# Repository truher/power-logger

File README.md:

# Power Logger

Multichannel logger for residential power consumption measurement.
Reads two legs of 120v and a whole log of inductive current measurements.
Uses interrupts on the Teensy to avoid phase error.

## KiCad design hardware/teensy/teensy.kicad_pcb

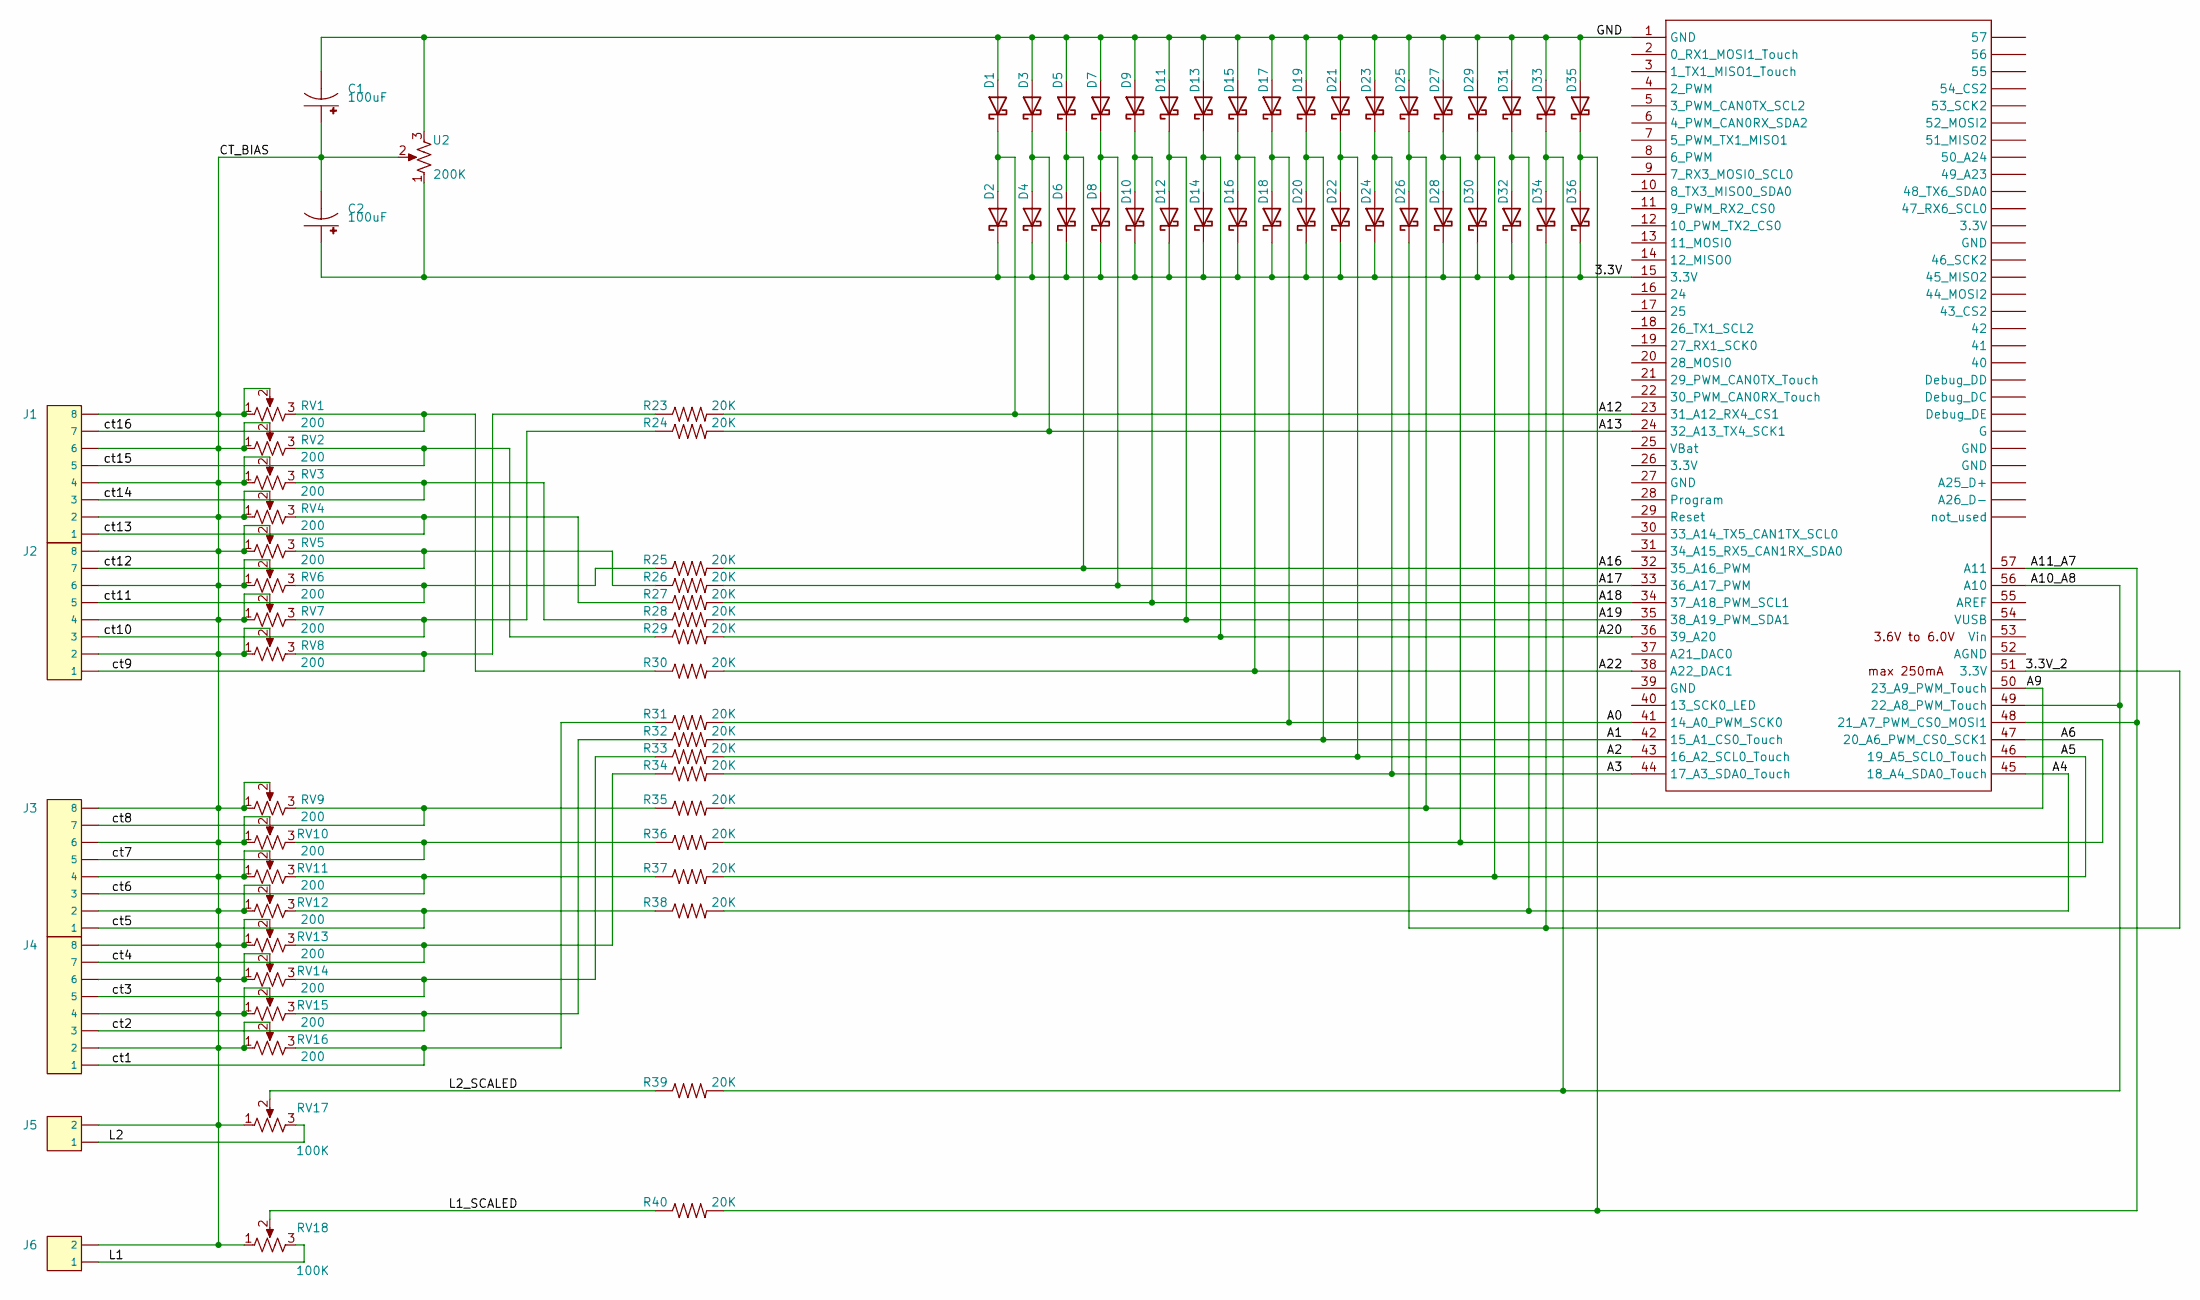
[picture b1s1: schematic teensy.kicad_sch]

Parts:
C1, C2: 100uF; CPOL-RADIAL-5MM-10MM
D1, D2, D3, D4, D5, D6, D7, D8, D9, D10, D11, D12, D13, D14, D15, D16, D17, D18, D19, D20, D21, D22, D23, D24, D25, D26, D27, D28, D29, D30, D31, D32, D33, D34, D35, D36: D_SOD-123
J1, J2, J3, J4: 1X08
J5, J6: 1X02
R23, R24, R25, R26, R27, R28, R29, R30, R31, R32, R33, R34, R35, R36, R37, R38, R39, R40: 20K; AXIAL-0.3
RV1, RV2, RV3, RV4, RV5, RV6, RV7, RV8, RV9, RV10, RV11, RV12, RV13, RV14, RV15, RV16: 200; Potentiometer_Bourns_3296W_Vertical
RV17, RV18: 100K; Potentiometer_Bourns_3296W_Vertical
U1: Teensy3.5; Teensy35_36_EMON
U2: 200K; Potentiometer_Bourns_3296W_Vertical

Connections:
/3.3V: C2.+, D2.1 (K), D4.1 (K), D6.1 (K), D8.1 (K), D10.1 (K), D12.1 (K), D14.1 (K), D16.1 (K), D18.1 (K), D20.1 (K), D22.1 (K), D24.1 (K), D28.1 (K), D30.1 (K), D32.1 (K), D36.1 (K), U1.15 (3.3V), U2.1
/3.3V_2: D26.1 (K), D34.1 (K), U1.51 (3.3V)
/A0: D17.1 (K), D18.2 (A), R31.P$2 (2), U1.41 (14_A0_PWM_SCK0)
/A1: D19.1 (K), D20.2 (A), R32.P$2 (2), U1.42 (15_A1_CS0_Touch)
/A2: D21.1 (K), D22.2 (A), R33.P$2 (2), U1.43 (16_A2_SCL0_Touch)
/A3: D23.1 (K), D24.2 (A), R34.P$2 (2), U1.44 (17_A3_SDA0_Touch)
/A4: D31.1 (K), D32.2 (A), R38.P$2 (2), U1.45 (18_A4_SDA0_Touch)
/A5: D29.1 (K), D30.2 (A), R37.P$2 (2), U1.46 (19_A5_SCL0_Touch)
/A6: D27.1 (K), D28.2 (A), R36.P$2 (2), U1.47 (20_A6_PWM_CS0_SCK1)
/A9: D25.1 (K), D26.2 (A), R35.P$2 (2), U1.50 (23_A9_PWM_Touch)
/A10_A8: D33.1 (K), D34.2 (A), R39.P$2 (2), U1.49 (22_A8_PWM_Touch), U1.56 (A10)
/A11_A7: D35.1 (K), D36.2 (A), R40.P$2 (2), U1.48 (21_A7_PWM_CS0_MOSI1), U1.57 (A11)
/A12: D1.1 (K), D2.2 (A), R23.P$2 (2), U1.23 (31_A12_RX4_CS1)
/A13: D3.1 (K), D4.2 (A), R24.P$2 (2), U1.24 (32_A13_TX4_SCK1)
/A16: D5.1 (K), D6.2 (A), R25.P$2 (2), U1.32 (35_A16_PWM)
/A17: D7.1 (K), D8.2 (A), R26.P$2 (2), U1.33 (36_A17_PWM)
/A18: D9.1 (K), D10.2 (A), R27.P$2 (2), U1.34 (37_A18_PWM_SCL1)
/A19: D11.1 (K), D12.2 (A), R28.P$2 (2), U1.35 (38_A19_PWM_SDA1)
/A20: D13.1 (K), D14.2 (A), R29.P$2 (2), U1.36 (39_A20)
/A22: D15.1 (K), D16.2 (A), R30.P$2 (2), U1.38 (A22_DAC1)
/CT_BIAS: C1.+, C2.-, J1.2, J1.4, J1.6, J1.8, J2.2, J2.4, J2.6, J2.8, J3.2, J3.4, J3.6, J3.8, J4.2, J4.4, J4.6, J4.8, J5.2, J6.2, RV1.1, RV1.2, RV2.1, RV2.2, RV3.1, RV3.2, RV4.1, RV4.2, RV5.1, RV5.2, RV6.1, RV6.2, RV7.1, RV7.2, RV8.1, RV8.2, RV9.1, RV9.2, RV10.1, RV10.2, RV11.1, RV11.2, RV12.1, RV12.2, RV13.1, RV13.2, RV14.1, RV14.2, RV15.1, RV15.2, RV16.1, RV16.2, RV17.1, RV18.1, U2.2
/GND: C1.-, D1.2 (A), D3.2 (A), D5.2 (A), D7.2 (A), D9.2 (A), D11.2 (A), D13.2 (A), D15.2 (A), D17.2 (A), D19.2 (A), D21.2 (A), D23.2 (A), D25.2 (A), D27.2 (A), D29.2 (A), D31.2 (A), D33.2 (A), D35.2 (A), U1.1 (GND), U2.3
/L1: J6.1, RV18.3
/L1_SCALED: R40.P$1 (1), RV18.2
/L2: J5.1, RV17.3
/L2_SCALED: R39.P$1 (1), RV17.2
/ct1: J4.1, R31.P$1 (1), RV16.3
/ct2: J4.3, R32.P$1 (1), RV15.3
/ct3: J4.5, R33.P$1 (1), RV14.3
/ct4: J4.7, R34.P$1 (1), RV13.3
/ct5: J3.1, R38.P$1 (1), RV12.3
/ct6: J3.3, R37.P$1 (1), RV11.3
/ct7: J3.5, R36.P$1 (1), RV10.3
/ct8: J3.7, R35.P$1 (1), RV9.3
/ct9: J2.1, R23.P$1 (1), RV8.3
/ct10: J2.3, R24.P$1 (1), RV7.3
/ct11: J2.5, R25.P$1 (1), RV6.3
/ct12: J2.7, R26.P$1 (1), RV5.3
/ct13: J1.1, R27.P$1 (1), RV4.3
/ct14: J1.3, R28.P$1 (1), RV3.3
/ct15: J1.5, R29.P$1 (1), RV2.3
/ct16: J1.7, R30.P$1 (1), RV1.3

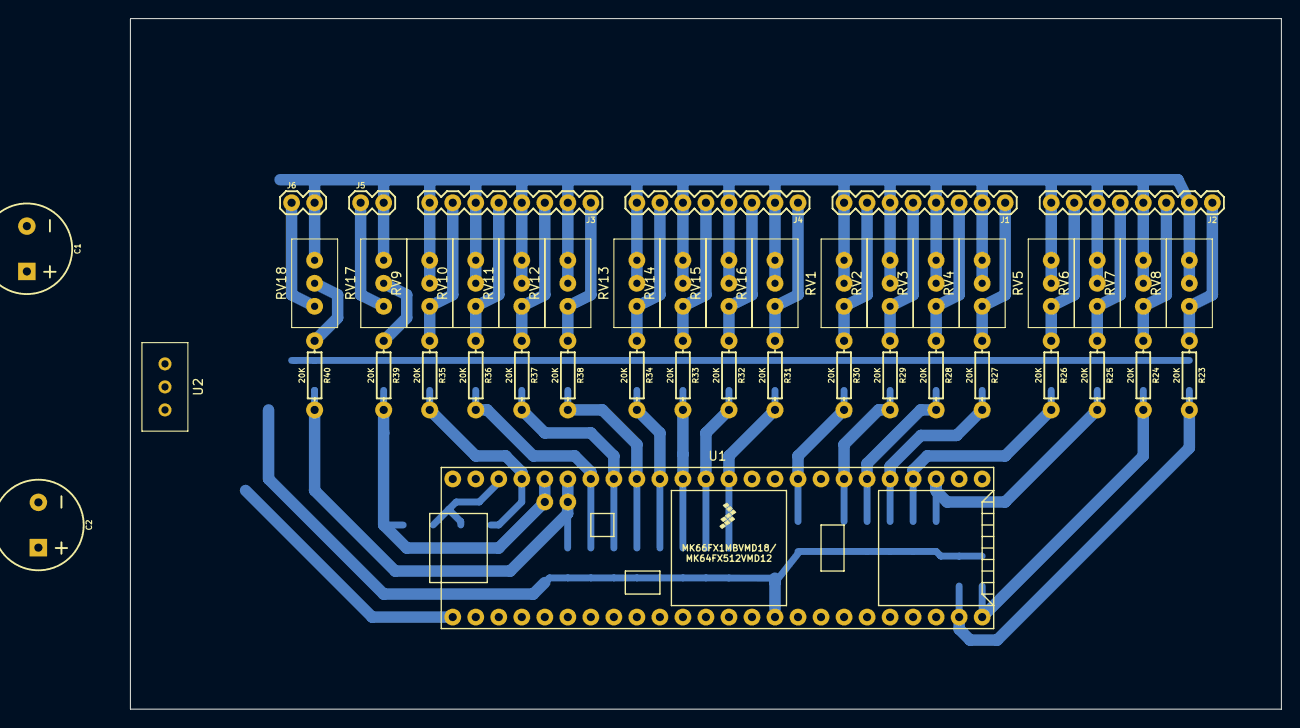
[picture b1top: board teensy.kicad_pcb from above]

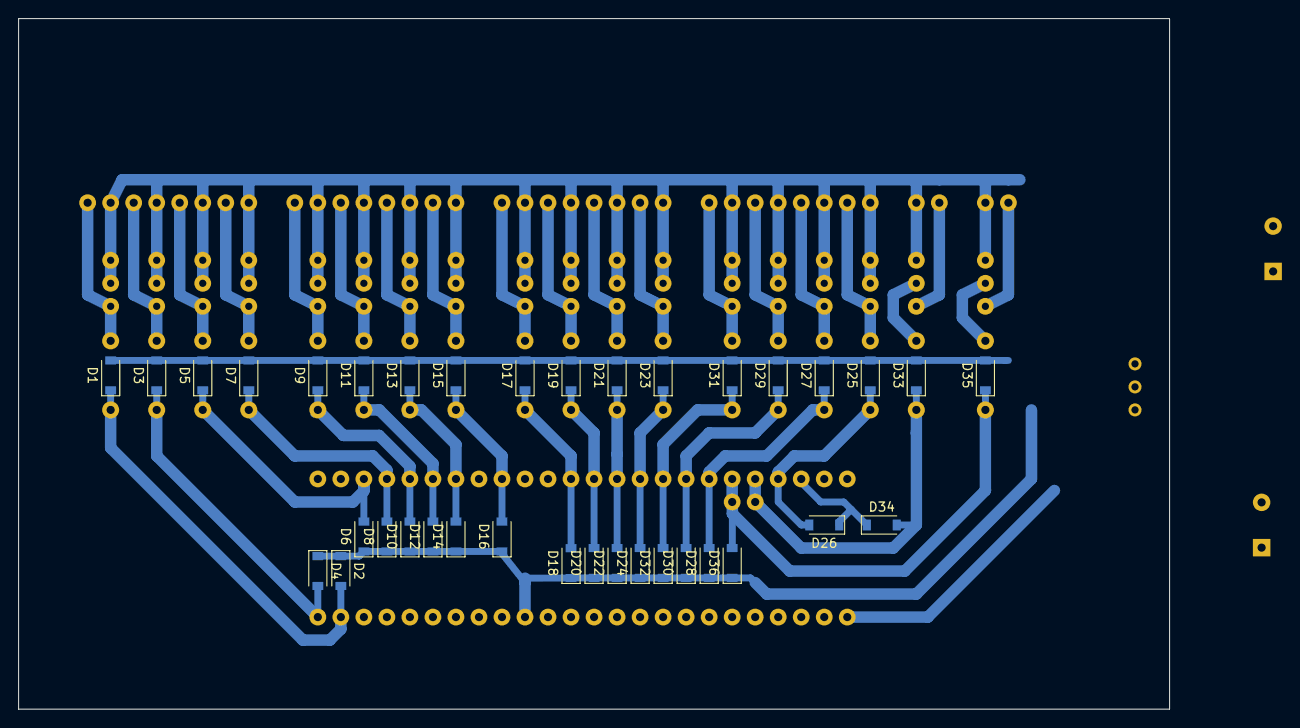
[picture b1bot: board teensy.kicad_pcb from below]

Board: 2 copper layers, 127.0 x 76.2 mm, 82 parts (36 on the bottom side), 42 nets.

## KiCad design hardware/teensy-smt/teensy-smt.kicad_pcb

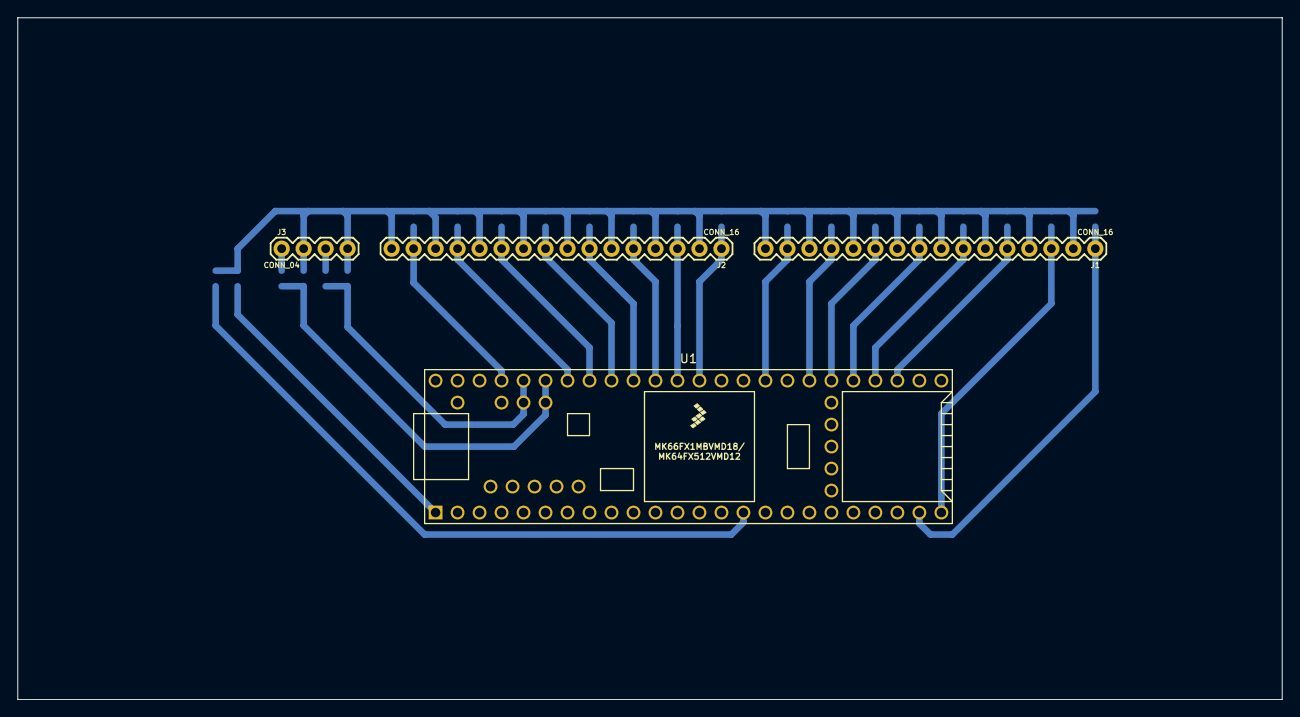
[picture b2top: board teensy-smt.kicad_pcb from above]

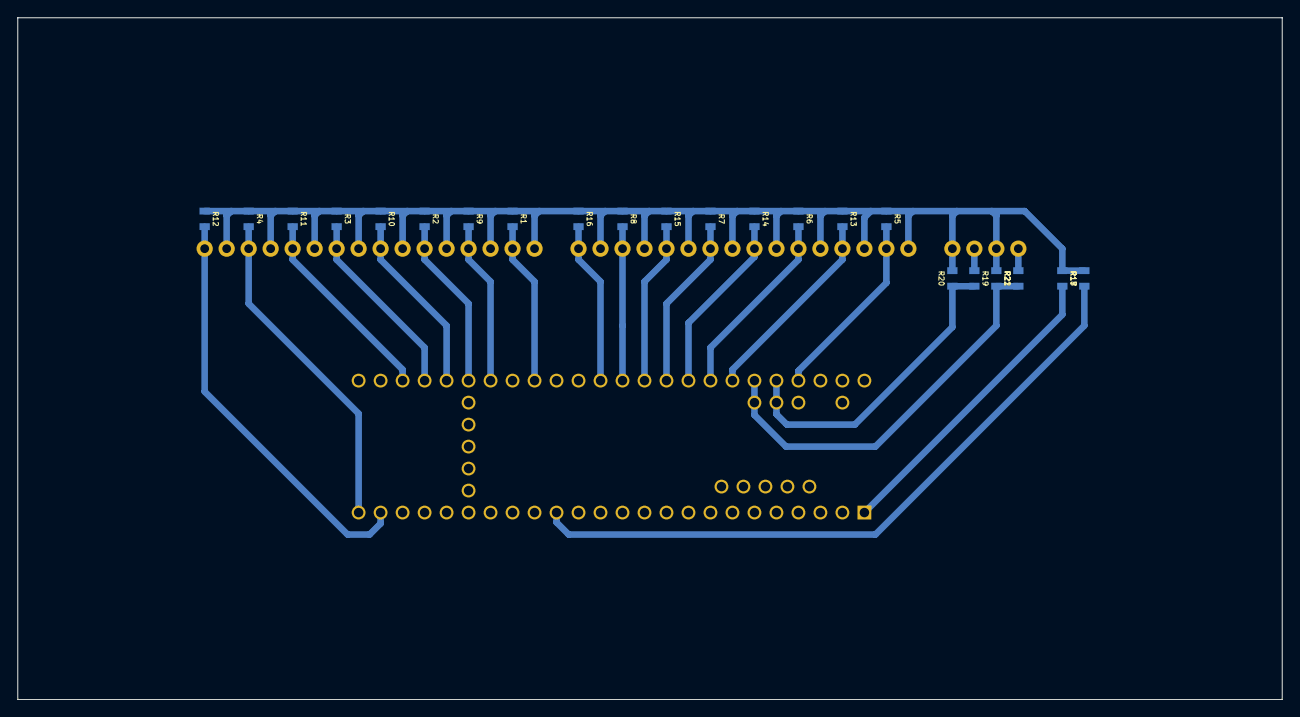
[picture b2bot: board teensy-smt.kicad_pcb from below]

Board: 2 copper layers, 146.1 x 78.7 mm, 26 parts (22 on the bottom side), 23 nets.

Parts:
J1, J2: CONN_16; 1X16
J3: CONN_04; 1X04
R1, R2, R3, R4, R5, R6, R7, R8, R9, R10, R11, R12, R13, R14, R15, R16, R17, R18, R19, R20, R21, R22: 0805
U1: Teensy3.5; Teensy35_36

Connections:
/3.3V: R17.1, U1.15 (3.3V)
/CT_BIAS: J1.2, J1.4, J1.6, J1.8, J1.10, J1.12, J1.14, J1.16, J2.2, J2.4, J2.6, J2.8, J2.10, J2.12, J2.14, J2.16, J3.2, J3.4, R1.1, R2.1, R3.1, R4.1, R5.1, R6.1, R7.1, R8.1, R9.1, R10.1, R11.1, R12.1, R13.1, R14.1, R15.1, R16.1, R17.2, R18.1, R20.2, R21.1
/GND: R18.2, U1.1 (GND)
/L1: J3.1, R22.2
/L1_SCALED: R21.2, R22.1, U1.48 (21_A7_PWM_CS0_MOSI1), U1.57 (A11)
/L2: J3.3, R19.1
/L2_SCALED: R19.2, R20.1, U1.49 (22_A8_PWM_Touch), U1.56 (A10)
/ct1: J2.1, R16.2, U1.41 (14_A0_PWM_SCK0)
/ct2: J2.3, R8.2, U1.42 (15_A1_CS0_Touch)
/ct3: J2.5, R15.2, U1.43 (16_A2_SCL0_Touch)
/ct4: J2.7, R7.2, U1.44 (17_A3_SDA0_Touch)
/ct5: J2.9, R14.2, U1.45 (18_A4_SDA0_Touch)
/ct6: J2.11, R6.2, U1.46 (19_A5_SCL0_Touch)
/ct7: J2.13, R13.2, U1.47 (20_A6_PWM_CS0_SCK1)
/ct8: J2.15, R5.2, U1.50 (23_A9_PWM_Touch)
/ct9: J1.1, R12.2, U1.23 (31_A12_RX4_CS1)
/ct10: J1.3, R4.2, U1.24 (32_A13_TX4_SCK1)
/ct11: J1.5, R11.2, U1.32 (35_A16_PWM)
/ct12: J1.7, R3.2, U1.33 (36_A17_PWM)
/ct13: J1.9, R10.2, U1.34 (37_A18_PWM_SCL1)
/ct14: J1.11, R2.2, U1.35 (38_A19_PWM_SDA1)
/ct15: J1.13, R9.2, U1.36 (39_A20)
/ct16: J1.15, R1.2, U1.38 (A22_DAC1)

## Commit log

2020-04-05 matplotlib demo
2020-04-10 fiddling with plots
2020-04-10 more plot fixes
2020-04-10 add usb logger
2020-04-11 fix logger
2020-04-11 fix gitignore
2020-04-12 logger now hot pluggable
2020-04-12 fixed-width time
2020-04-13 now also read the datafile, using inotify
2020-04-13 clean up parsing and validation
2020-04-16 fiddling with plotting
2020-04-16 more plot fiddling
2020-04-16 minor fixes
2020-04-16 grouping
2020-04-16 commit experiments
2020-04-16 add example test
2020-04-16 multi-series experiment
2020-04-16 extract random generator
2020-04-16 comment test data
2020-04-17 example test
2020-04-17 move rollup to lib, test it
2020-04-17 removed, it was an exploration into the wrong way
2020-04-17 removed, superceded by later scripts
2020-04-17 remove plot example
2020-04-17 rename test data file
2020-04-17 remove plot experiment
2020-04-17 abandon mixed frequency resampling
2020-04-17 multiple threads, one frame? nah.
2020-04-17 remove file IO experiment
2020-04-17 formatting
2020-04-17 add multi-sensor random data
2020-04-18 add multi-sensor summarization, plot not done yet
2020-04-18 multi sensor plot works
2020-04-18 add monthly table
2020-04-18 don't pivot
2020-04-18 moving stuff to lib
2020-04-19 periodic summarizer works
2020-04-19 fix date format
2020-04-19 no more inotify
2020-04-19 rename
2020-04-19 move random data producers into standalone scripts
2020-04-19 remove single-sensor plotting
2020-04-21 mv to py dir
2020-04-22 very simple arduino now
2020-04-26 timer interrupt for sampling
    instead of running open-loop, use one of the avr timers in CTC
    mode, to interrupt exactly every 50us, so i don't have to keep
    the observation timestamps, and so can fit more observations
    in ram.
2020-04-26 hot-plug sensor usb faster
2020-04-26 handle v and i with timing offsets
2020-04-26 put the timeout back the way it was
    the short timeout results in partial lines i don't want to deal with
2020-04-26 fooling with delta encoding
2020-04-26 fix signed hex and fallthrough bugs
2020-04-26 decode delta and explode
2020-04-26 offset timing
2020-04-26 nice charts all done
2020-04-26 better handle error rows
2020-04-30 many small things
2020-04-30 performance testing
2020-05-03 got d3fc webgl rendering working
2020-05-03 performance testing python serialization
2020-05-03 checkpoint many small changes
2020-05-03 one more small change
2020-05-03 made webgl multis work with python data
    still not fast, but whatever, it can do ~10fps with some jank
2020-05-03 fix mypy
2020-05-04 works well enough at 10fps
    also handles partial data messages
2020-05-04 cleanups
2020-05-04 fix types
2020-05-04 cleaned up performance benchmarks
2020-05-04 woo, fixed d3fc error, now webgl goes 30fps
2020-05-05 little changes, no need for full fps
    it goes 4 fps with no real load anywhere
2020-05-05 remove obsolete demos
2020-05-06 working to finish the stuff in demo2
2020-05-06 more cleanups
2020-05-07 move stuff into lib
2020-05-07 hooked up sensors to VI charts, not fully
2020-05-07 multiple loads hooked up
2020-05-07 slower updates
2020-05-08 sensors now update archival data
    still messy and slow
2020-05-10 wrestling with d3 for awhile
2020-05-10 blag
2020-05-10 now works with server data
2020-05-10 cleanup
2020-05-10 moved summary charts to summary.html
2020-05-10 render three charts
2020-05-10 remove extra files
2020-05-10 working on rollups
2020-05-10 multiple graphs and summary table
    with correct windows.
2020-05-11 three pages working
    utc still broken
2020-05-11 combined css/js/html
2020-05-11 removed matplotlib
2020-05-11 fix test data
2020-05-11 add lib class to wrap serial readline
2020-05-12 add queue to transcriber
    still single thread
2020-05-12 separated reader and writer
2020-05-12 move interpolation etc out of transcribe
2020-05-12 removed transcriber
2020-05-12 oops, one more deletion
2020-05-12 threaded reads work
    consumer can be arbitrarily slow, but no corruption
2020-05-13 reduced cpu load by 10X, by sleeping between reads
    threaded reader was spinning faster than the sender
2020-05-14 simplify CSS
2020-05-15 got multis working better
2020-05-15 cleaned up js code
2020-05-15 remove demo code for sample interpolation
2020-05-15 remove another interp demo
2020-05-15 rm fastlogger
2020-05-15 clean up tests and test data
2020-05-15 move demos to demo repo
2020-05-15 rename test
2020-05-16 linted arduino, found i was overrunning sprintf
2020-05-16 stop using orjson, it doesn't work on ARM
2020-05-17 fixed everything pylint complained about
2020-05-17 remove obsolete test scripts
2020-05-18 speed up serialization
    larger buffer, fewer writes => less USB overhead
2020-05-18 was experimenting with shorter messages
    yes, overhead scales with message length.
2020-05-18 raw stats page, also cleanups
2020-05-18 fix js error
2020-05-22 make the emontx shield LED flash :-)
2020-05-22 looking harder at V and I
    multi graphs for "raw", zero = average, etc
2020-05-23 calibration done, graphs prettier, mypy happy
2020-05-23 fixed window in raw
    otherwise the trimmer makes it change all at once
2020-06-08 add mega shield schematic
2020-06-08 add schematic png
2020-06-09 replace ngspice components with real ones
2020-06-09 first cut at the board
2020-06-09 removed all but one LED
2020-06-09 replace pair terminals with separate pos/neg
2020-06-09 component placement done
2020-06-10 traces done, gnd plane done
2020-06-13 fix lib test
2020-06-13 beginning to move to mega
2020-06-14 remove the test stuff from config
2020-07-03 figured out FTM on teensy
2020-07-04 more progress
    FTM triggers an interrupt (to print) and both ADCs.
    when ADCs are done, they trigger an interrupt to extract the
    values.
    DMA is not started
2020-07-04 now DMA works
    so, timer -> ADC -> DMA, one buffer per USB input
2020-07-05 yay, it works now
    bunches of 1000 samples from 2 synchronized channels, yay!
2020-07-05 cleaned up, verified with scope, works great.
    two sync'ed channel ADC with DMA, sample timing uses timer,
    batch timing is not controlled.
2020-07-06 now outputs base85 from arduino
    tried decoding a few with python, works fine.
2020-07-06 oops, remove the old printing
2020-07-06 hooked up teensy to the python part
    threw out the interpolation stuff, works fine, just one ADC though.
2020-07-06 one led flash per sample, not toggled
2020-07-06 remove AVR arduino
2020-07-06 use teensy arduino
2020-07-06 starting to fix the lint
2020-07-06 more linting
2020-07-06 lint all done
2020-07-08 partial on-the-fly configuration of ADC parameters
2020-07-08 variable length now works
    but not yet in the web UI
2020-07-09 a bit more on config
2020-07-09 add variable freq
2020-07-10 prevent overflow
2020-07-12 calibrated ADC frequencies
    1khz to 150khz seems to work, single-ended.
2020-07-12 fixed sample timing
    the teensy code default is 4x averaging, so i turned that off
    now it goes about 500khz, 2us sample time, plenty of noise at
    that speed, but whatever.
2020-07-13 front end can adjust freq and length
    and updates at a reasonable rate as well
2020-07-14 adding channel details
2020-07-14 a bit more progress on channels
2020-07-15 finished channels
    they seem to work, need to test them.
2020-07-15 moved to ftm1 to make room for a8
2020-07-16 a little cleanup
2020-07-16 playing with kicad
2020-07-17 still learning kicad
2020-07-17 added more to sch
2020-07-17 more wiring
2020-07-18 fully routed
    ugly, but correct, i think.
2020-07-18 good looking board now
2020-07-19 sch and pcb look good, also gbr and ngc outputs
2020-07-19 fiddling with pcb2gcode
2020-07-21 hoo boy, adc protection and bigger terminals
2020-07-21 layout
2020-07-22 prettier traces, removed smt thing
2020-07-22 a little more beauty
2020-07-23 updated gbr and ngc
2020-07-25 DXF files
2020-07-25 add "map" file
2020-07-26 better gcodes
2020-07-29 whoops, lower zchange
2020-07-29 lower feed, smaller bit, more passes
2020-07-29 back to zero extra passes
2020-08-08 disable optimize
2020-08-08 retract 0.1, nog64
2020-08-08 faster feed, don't wait for spindle spin up or down
2020-08-08 add post-processor to remove M6
2020-08-08 less z
2020-08-08 remove M0
2020-08-08 remove a few more unnecessary gcode commands
2020-08-08 50 thou is way too deep
2020-08-09 bigger pads, bigger mill
2020-08-09 many more passes
2020-08-09 pcb is more than 10 thou thick
2020-08-09 remove offending M6 from drill
2020-08-09 got outline working
2020-08-09 add outline bridges
2020-08-10 2.54 rather than 3.5mm screws, now fits in 3x5
2020-08-23 removed some resistors i don't need
2020-08-23 moved a few traces
2020-08-23 gerbers
2020-09-06 settings for 0.1 cutters
    slower, finer
2020-09-06 minor tweaks
2020-09-06 wider cuts, fewer of them, deeper
2020-09-07 accommodate actual 27 mil bit
2020-09-07 tweaking after first copper run
2020-09-08 add workholding gcode
2020-09-10 add tooling cutout
2020-09-11 faster deeper
2020-09-12 tweaks
    mostly annoyed with ragged edges; try shallower, conventional cut
2020-10-05 formatting for printing
2020-10-12 fix js references
2020-10-12 use correct teensy ID number
2020-10-12 why does DAC1_C0 crash the teensy?
2020-10-12 correct decode method name
2020-10-13 arduino channels now match hardware
    i changed the routing to make it easier to lay out
2020-10-14 fixed channel config
    differential was on the wrong channel, also reported on wrong output
2020-10-17 ignore first few samples since they're bad
    at least the first one is. ignoring 4 makes b85 happy.
2020-10-17 add capacitor for bias smoothing
2020-10-24 add median
    haven't used it yet
2020-10-24 various filtering attempts
2020-10-24 use std kth_element instead of my own quickselect
2020-10-25 tweaking to reduce noise
2020-10-25 remove filtering/phase correction
2020-10-25 phase lag both V and A
2020-11-08 fix the kicad, also tuning
